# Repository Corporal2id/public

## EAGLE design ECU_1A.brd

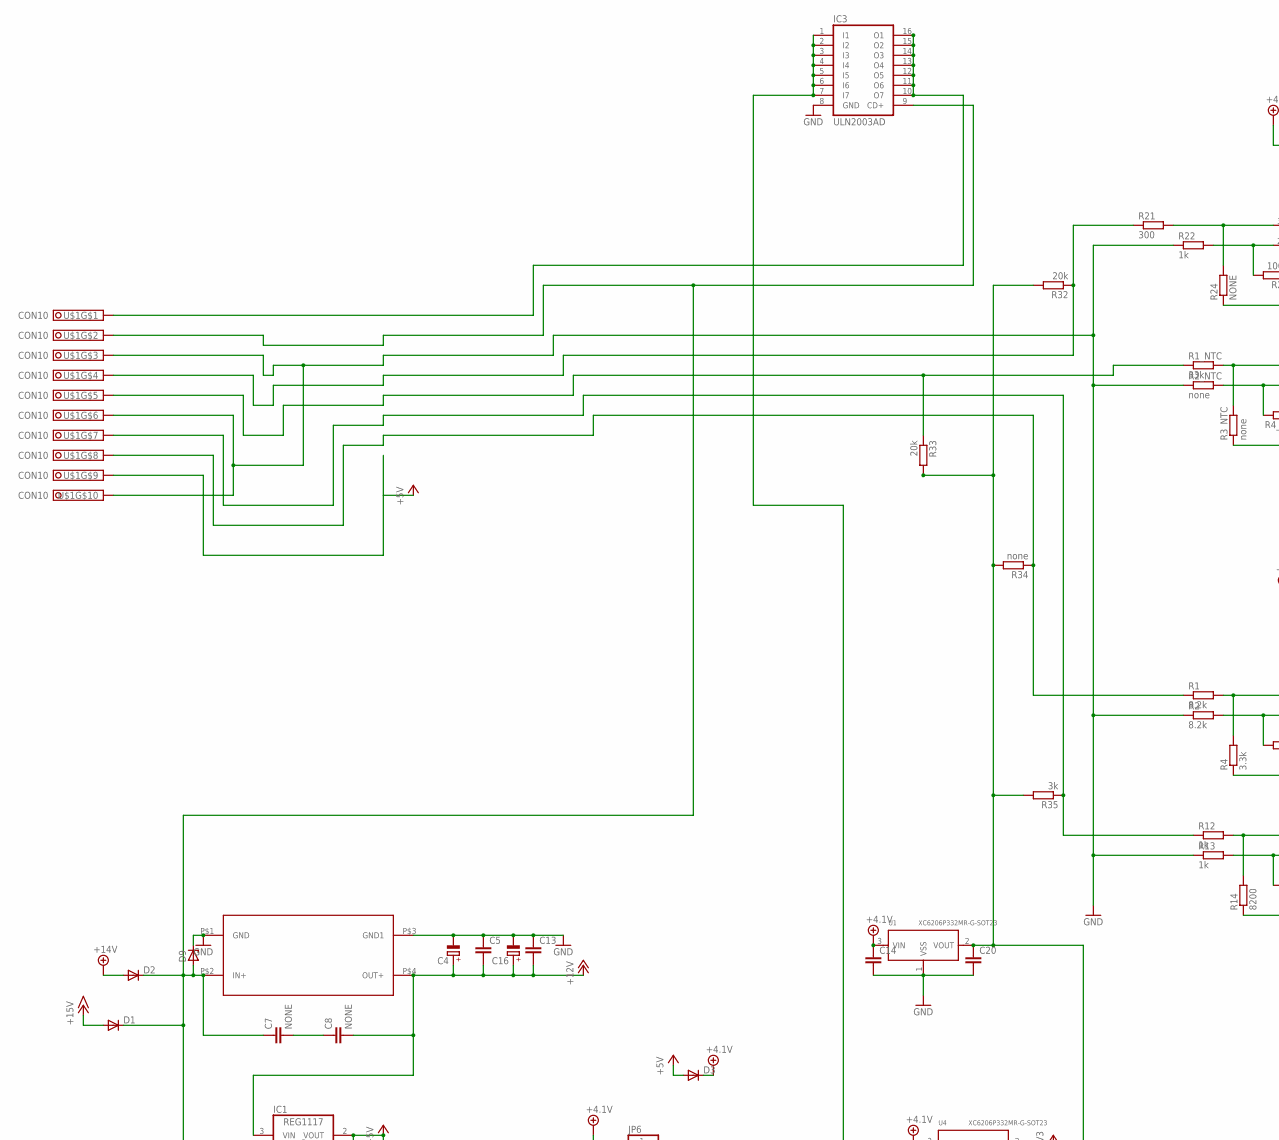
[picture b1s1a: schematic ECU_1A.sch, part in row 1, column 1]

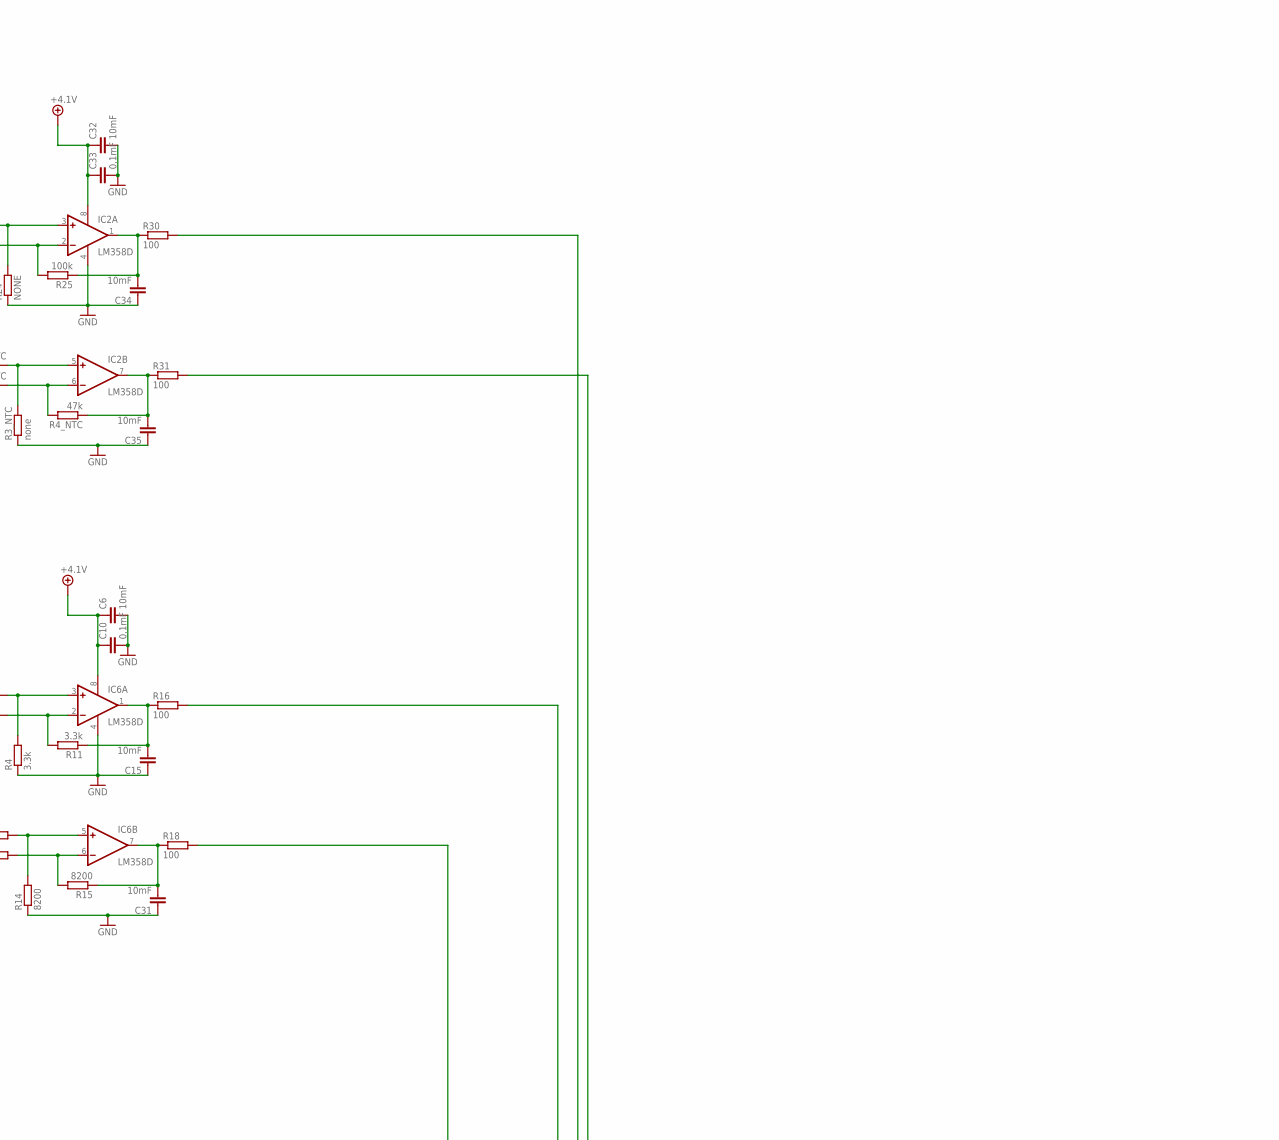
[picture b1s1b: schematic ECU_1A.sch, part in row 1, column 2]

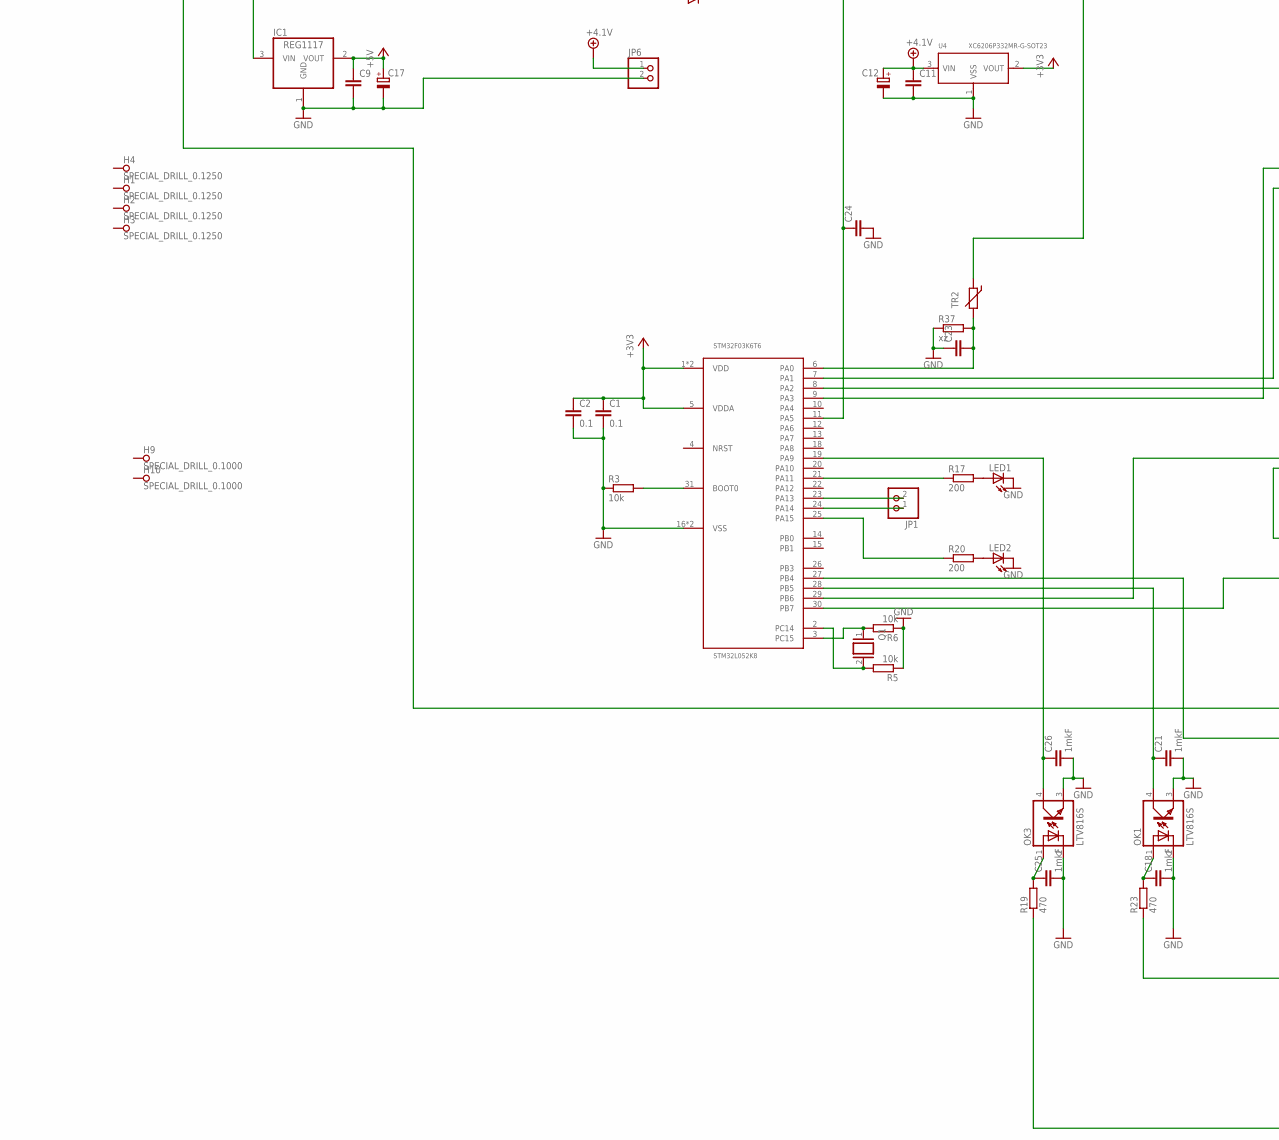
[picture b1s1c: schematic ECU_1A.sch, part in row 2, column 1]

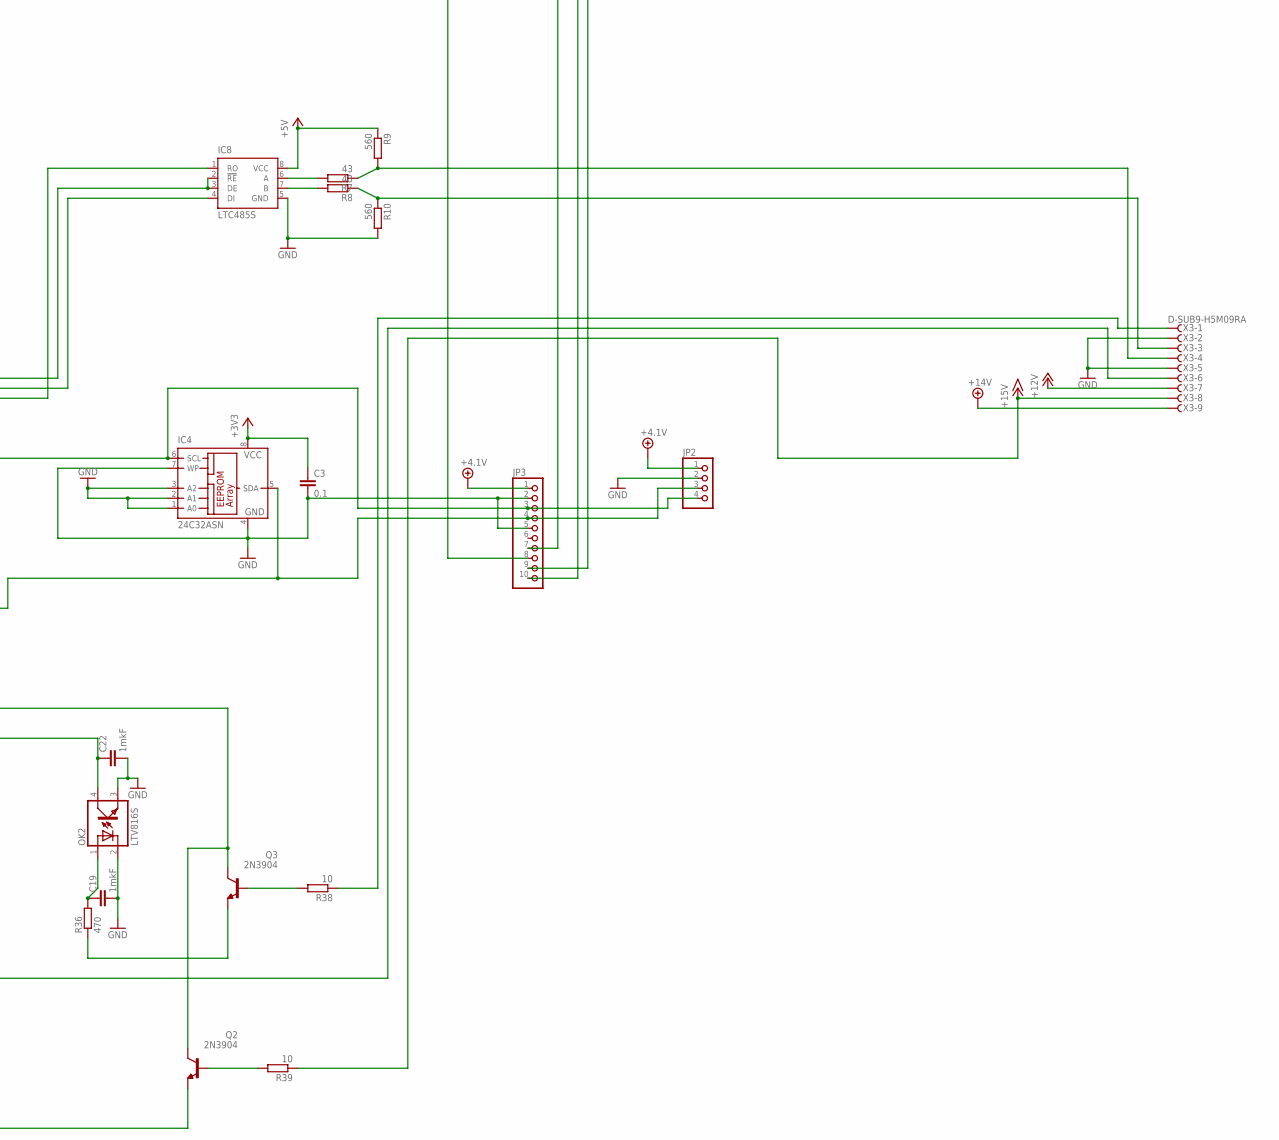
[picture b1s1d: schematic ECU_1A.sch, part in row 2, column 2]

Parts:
C1, C2, C3: 0.1; C0805
C4, C12: CPOL-EUE2.5-6; E2,5-6
C5, C9, C11, C13, C14, C20, C23, C24: C-EUC0805; C0805
C6, C15, C31, C32, C34, C35: 10mF; C0805
C7, C8: NONE; C0805
C10, C33: 0,1mF; C0805
C16: CPOL-EUE5-10.5; E5-10,5
C17: CPOL-EUE2,5-6E; E2,5-6E
C18, C19, C21, C22, C25, C26: 1mkF; C0805
D1, D2, D3: DIODE-DO-214AC; DO-214AC
D9: ZENER-DIODEZD-7.5; ZDIO-7.5
H1, H2, H3, H4: SPECIAL_DRILL_0.1250; PAD_0.1250
H9, H10: SPECIAL_DRILL_0.1000; PAD_0.1000
IC1: REG1117; SOT223
IC2, IC6: LM358D; SO08
IC3: ULN2003AD; SO16
IC4: 24C32ASN; SO-08
IC8: LTC485S; SOIC8
JP1, JP6: PINHD-1X2; 1X02
JP2: PINHD-1X4; 1X04
JP3: PINHD-1X10; 1X10
LED1, LED2: LEDCHIPLED_1206; CHIPLED_1206
OK1, OK2, OK3: LTV816S; SMD4
Q1: XTAL/S; QS
Q2, Q3: 2N3904; TO92
R1, R2: 8.2k; R0805
R1_NTC: 33k; R0805
R2_NTC, R3_NTC, R34: none; R0805
R3, R5, R6: 10k; R0805
R4, R11: 3.3k; R0805
R4_NTC: 47k; R0805
R7, R8: 43; R0805
R9, R10: 560; R0805
R12, R13, R22: 1k; R0805
R14, R15: 8200; R0805
R16, R18, R30, R31: 100; R0805
R17, R20: 200; R0805
R19, R23, R36: 470; R0805
R21: 300; R0805
R24: NONE; R0805
R25: 100k; R0805
R32, R33: 20k; R0805
R35: 3k; R0805
R37: xz; R0805
R38, R39: 10; R0805
STM32F03K6T6: STM32L052K8; LQFP32-7X7
TR2: THERMISTOR_R-2,5; RS-2,5
U1, U4: XC6206P332MR-G-SOT23; SOT-23
U$1: CON10
U$2: DC24_DC5; SLIM_MOUNT
X3: D-SUB9-H5M09RA; H5M09RA

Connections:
3.3V_SENSORS: C20.1, R32.2, R33.2, R34.2, R35.2, TR2.1, U1.2 (VOUT)
+3V3: C1.1, C2.1, C3.1, IC4.8 (VCC), STM32F03K6T6.1 (VDD), STM32F03K6T6.5 (VDDA), STM32F03K6T6.17 (VDD), U4.2 (VOUT)
+4.1V: C6.1, C10.1, C11.1, C12.+, C14.1, C32.1, C33.1, D3.C, IC2.8 (V+), IC6.8 (V+), JP2.1, JP3.1, JP6.1, U1.3 (VIN), U4.3 (VIN)
+5V: C9.1, C17.+, D3.A, IC1.2 (VOUT), IC8.8 (VCC), R9.1, U$1.9
+12V: C4.+, C5.2, C8.2, C13.2, C16.+, IC1.3 (VIN), U$2.P$4 (OUT+), X3.7
+14V: D2.A, X3.9
+15V: D1.A, R39.1, X3.8
A: IC8.6 (A), R7.2
A1_5V_PRESS: JP3.7, R16.2
A3_NTC_10K: JP3.9, R31.2
A4_TERMO_K-TYPE: JP3.10, R30.2
AIN_3: R1_NTC.1, R33.1, U$1.5
AIN_4: R21.1, R32.1, U$1.4
B: IC8.7 (B), R8.2
DE_UART: IC8.2 (!RE), IC8.3 (DE), STM32F03K6T6.7 (PA1)
DI1_IN: C21.1, OK1.4 (COL), STM32F03K6T6.28 (PB5)
DI2_IN: C22.1, OK2.4 (COL), STM32F03K6T6.27 (PB4)
DI3_IN: C26.1, OK3.4 (COL), STM32F03K6T6.19 (PA9)
DI_1: R23.1, X3.6
DI_2: R38.1, X3.1
FLVL: JP3.8, R18.2
GND: C1.2, C2.2, C3.2, C4.-, C5.1, C6.2, C9.2, C10.2, C11.2, C12.-, C13.1, C14.2, C15.1, C16.-, C17.-, C18.2, C19.2, C20.2, C21.2, C22.2, C23.1, C24.2, C25.2, C26.2, C31.1, C32.2, C33.2, C34.1, C35.1, D9.C, IC1.1 (GND), IC2.4 (V-), IC3.8 (GND), IC4.1 (A0), IC4.2 (A1), IC4.3 (A2), IC4.4 (GND), IC4.7 (WP), IC6.4 (V-), IC8.5 (GND), JP2.2, JP3.2, JP3.5, JP6.2, LED1.C, LED2.C, OK1.2 (C), OK1.3 (EMIT), OK2.2 (C), OK2.3 (EMIT), OK3.2 (C), OK3.3 (EMIT), R2.1, R2_NTC.1, R3.1, R3_NTC.1, R4.1, R5.1, R6.1, R10.2, R13.1, R14.1, R22.1, R24.1, R37.1, STM32F03K6T6.16 (VSS), STM32F03K6T6.32 (VSS), U1.1 (VSS), U4.1 (VSS), U$1.3, U$1.6, U$1.10, U$2.P$1 (GND), U$2.P$3 (GND1), X3.2, X3.5
LED1: R17.1, STM32F03K6T6.21 (PA11)
LED2: R20.1, STM32F03K6T6.25 (PA15)
unnamed: Q1.2, R5.2, STM32F03K6T6.2 (PC14)
unnamed: C7.2, C8.1
unnamed: R3.2, STM32F03K6T6.31 (BOOT0)
unnamed: C25.1, OK3.1 (A), R19.2
unnamed: Q1.1, R6.2, STM32F03K6T6.3 (PC15)
unnamed: IC6.3 (+IN), R1.2, R4.2
unnamed: JP1.2, STM32F03K6T6.23 (PA13)
unnamed: LED1.A, R17.2
unnamed: LED2.A, R20.2
unnamed: C19.1, OK2.1 (A), R36.2
unnamed: C18.1, OK1.1 (A), R23.2
unnamed: IC6.2 (-IN), R2.2, R11.2
unnamed: C23.2, R37.2, STM32F03K6T6.6 (PA0), TR2.2
unnamed: JP1.1, STM32F03K6T6.24 (PA14)
unnamed: Q3.3 (E), R36.1
unnamed: Q3.2 (B), R38.2
unnamed: C15.2, IC6.1 (OUT), R11.1, R16.1
unnamed: R12.1, R35.1, U$1.7
unnamed: Q2.2 (B), R39.2
unnamed: IC2.3 (+IN), R21.2, R24.2
unnamed: IC6.5 (+IN), R12.2, R14.2
unnamed: IC6.6 (-IN), R13.2, R15.2
unnamed: R1.1, R34.1, U$1.8
unnamed: Q2.3 (E), R19.1
unnamed: C31.2, IC6.7 (OUT), R15.1, R18.1
unnamed: IC2.2 (-IN), R22.2, R25.2
unnamed: C34.2, IC2.1 (OUT), R25.1, R30.1
unnamed: IC2.5 (+IN), R1_NTC.2, R3_NTC.2
unnamed: IC2.6 (-IN), R2_NTC.2, R4_NTC.2
unnamed: C35.2, IC2.7 (OUT), R4_NTC.1, R31.1
PLUS_12: C7.1, D1.C, D2.C, D9.A, IC3.9 (CD+), Q2.1 (C), Q3.1 (C), U$1.2, U$2.P$2 (IN+)
REL: C24.1, IC3.1 (I1), IC3.2 (I2), IC3.3 (I3), IC3.4 (I4), IC3.5 (I5), IC3.6 (I6), IC3.7 (I7), STM32F03K6T6.11 (PA5)
RELAY_OUT: IC3.10 (O7), IC3.11 (O6), IC3.12 (O5), IC3.13 (O4), IC3.14 (O3), IC3.15 (O2), IC3.16 (O1), U$1.1
RS_A: R7.1, R9.2, X3.4
RS_B: R8.1, R10.1, X3.3
RX: IC8.1 (RO), STM32F03K6T6.9 (PA3)
SCL: IC4.6 (SCL), JP2.4, JP3.3, STM32F03K6T6.29 (PB6)
SDA: IC4.5 (SDA), JP2.3, JP3.4, STM32F03K6T6.30 (PB7)
TX: IC8.4 (DI), STM32F03K6T6.8 (PA2)

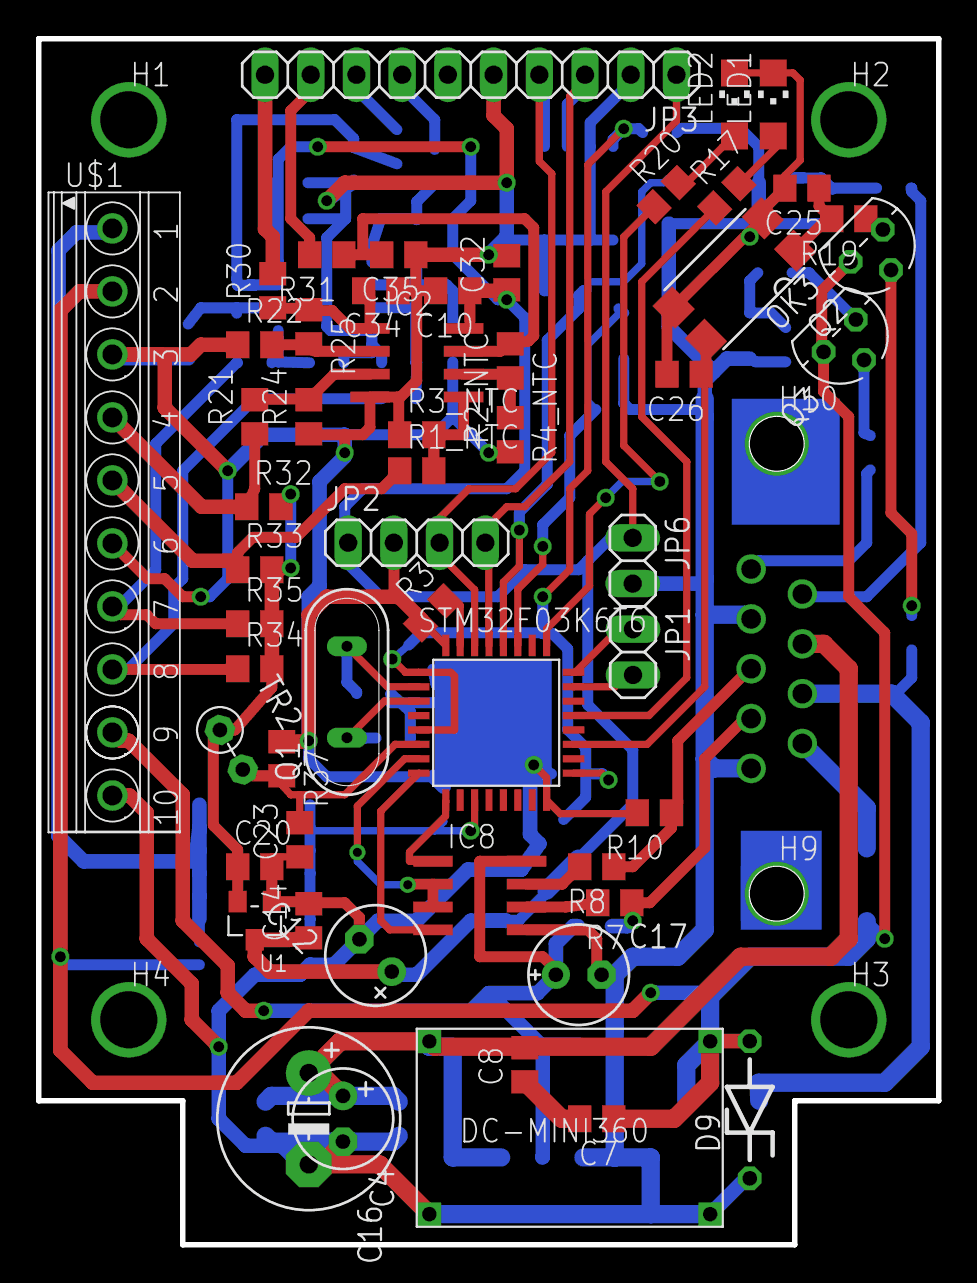
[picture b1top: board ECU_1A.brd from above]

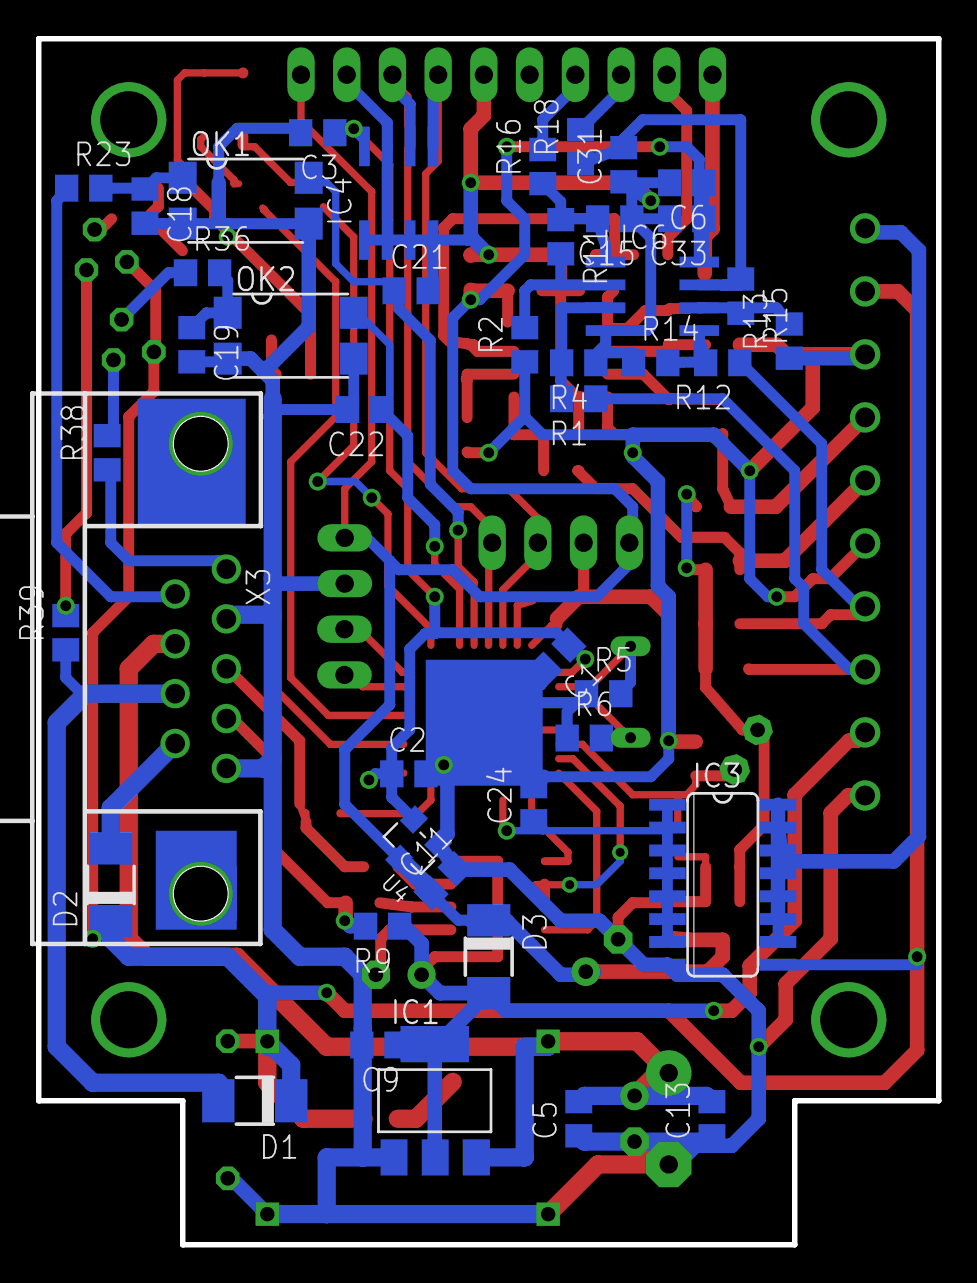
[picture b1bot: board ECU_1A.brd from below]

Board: 2 copper layers, 50.0 x 67.0 mm, 105 parts (44 on the bottom side), 63 nets.
